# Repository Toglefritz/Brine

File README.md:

# Brine

# Hello :wave:

Do you ever forget to refill the salt in your water softener? Yes you do. It is probably a safe
bet to say that everybody who has a water softener in their home forgets to refill the salt from
time to time. That "time to time" might even be several months in row.

The Brine water softener monitor keeps track of the amount of salt remaining in your water softener
and delivers alerts when the level is low. With this tool, you can keep your water softener filled
with salt and working properly, which, in turn, will keep your appliances free of mineral deposits,
your hands and hair well-moisturized, your laundry machine effective, and spots off your dishes.

# Overview 

Brine is an IoT water softener monitor. It tracks the amount of salt remaining in a water softener
and delivers alerts when the level is low, keeping your appliances free of mineral deposits, your
hands and hair well-moisturized, your laundry machine effective, and spots off your dishes.

The project spans hardware, firmware, a mobile companion app, cloud backend services, and a
marketing website.

## Project Status

> **Hardware finalization and pre-manufacturing**
>
> The hardware design is being finalized ahead of final system integration.
> Preparation for first-run manufacturing is underway.

## How It Works

A Brine device mounts inside the lid of a water softener, facing down toward the salt. It uses a
VL53L1X distance sensor to measure the distance from the top of the softener to the salt surface,
then calculates an approximate percentage of salt remaining. The device wakes from deep sleep once
every 24 hours to take a measurement, report it to the cloud, and go back to sleep.

Users set up a Brine device through the companion mobile app using Bluetooth Low Energy. The app
walks through pairing, WiFi provisioning, and account association. Once provisioned, the app
displays a dashboard with salt level, battery level, and device information, and delivers push
notifications when levels are low.

## Repository Structure

| Directory | Description |
|---|---|
| [`brine_app`](brine_app/) | Flutter companion app for iOS, Android, and macOS. Handles device provisioning via BLE and displays device status on a dashboard. |
| [`brine_firmware`](brine_firmware/) | ESP32 firmware built with PlatformIO and the Arduino framework. Manages the distance sensor, battery monitoring, BLE communication, and deep sleep. |
| [`brine_cloud_functions`](brine_cloud_functions/) | Firebase Cloud Functions that form the backend infrastructure. Handles device registration, data ingestion, and push notifications. |
| [`brine_website`](brine_website/) | Flutter web marketing site for the Brine product. |
| [`brine_docs`](brine_docs/) | Project documentation covering OTA updates, power management, provisioning, and security. |
| [`brine_electronics`](brine_electronics/) | PCB designs, Gerber files, prototypes, and reference materials for the Brine hardware. |
| [`brine_cad`](brine_cad/) | 3D models and drawings for the device enclosure (Plasticity, STEP, and STL formats). |
| [`brine_logos`](brine_logos/) | Brand assets and logo files in various formats. |
| [`brine_store_listings`](brine_store_listings/) | App store listing assets including screenshots and feature graphics. |
| [`brine_dev_tui`](brine_dev_tui/) | Terminal UI launcher for starting development tools (firmware flashing, emulator, serial monitor, Flutter app, Firebase emulator). |

## Development Launcher

The project includes a terminal UI for launching the various tools needed during local development.
Instead of remembering individual commands across multiple directories, the launcher provides a
single interface to start everything from one place.

Double-click `brine_dev_tui/Brine Launcher.command` in Finder to build and run it, or from the
terminal:

```sh
cd brine_dev_tui
go build -o brine-launcher .
./brine-launcher
```

See [`brine_dev_tui/README.md`](brine_dev_tui/README.md) for controls and architecture details.

## Technology Overview

- **Firmware**: C++ on ESP32 via PlatformIO / Arduino framework
- **Mobile App**: Flutter (Dart), targeting iOS, Android, and macOS
- **Backend**: Firebase (Cloud Functions, Firestore, Authentication, Cloud Messaging)
- **Website**: Flutter Web, hosted on Firebase Hosting
- **Hardware**: Custom PCB with ESP32 and VL53L1X distance sensor, powered by rechargeable LiPo battery
- **CAD**: Plasticity for enclosure design

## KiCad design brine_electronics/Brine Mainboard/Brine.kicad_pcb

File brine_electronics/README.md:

# Brine

PCB design and hardware reference for the Brine Monitor, an IoT device that monitors the amount of
salt remaining in a water softener.

## Hello :wave:

Do you ever forget to refill the salt in your water softener? Yes you do. It is probably a safe
bet to say that everybody who has a water softener in their home forgets to refill the salt from
time to time. That "time to time" might even be several months in row.

The Brine water softener monitor keeps track of the amount of salt remaining in your water softener
and delivers alerts when the level is low. With this tool, you can keep your water softener filled
with salt and working properly, which, in turn, will keep your appliances free of mineral deposits,
your hands and hair well-moisturized, your laundry machine effective, and spots off your dishes.

## Hardware Overview

The Brine device is a battery-powered sensor board built around a Seeed Studio XIAO ESP32-S3
module. It measures the distance from the top of a water softener to the salt surface using a
VL53L1X time-of-flight distance sensor, then reports that measurement to the cloud over WiFi.

The board includes:

- XIAO ESP32-S3 microcontroller module (WiFi, BLE, and GPIO)
- VL53L1X time-of-flight distance sensor connected over I2C
- Battery power input with a voltage divider for battery level monitoring
- A physical button for entering setup mode and waking from deep sleep
- An RGB LED for status indication during provisioning and operation

The PCB is a two-layer board designed to fit inside a custom enclosure. Enclosure models are
maintained separately in the [`brine_cad`](../brine_cad/) directory.

## KiCAD Project

The active design lives in the `Brine Mainboard/` directory and is a KiCAD 9 project.

### Hierarchical Schematic Structure

The schematic is organized as a set of hierarchical sheets. The root sheet (`Brine.kicad_sch`)
acts as a block diagram of the hardware, showing each functional block and the signals that
connect them. Each block is defined in its own schematic sheet with the full circuit detail for
that subsystem.

| Sheet | File | Description |
|---|---|---|
| Root | `Brine.kicad_sch` | Top-level block diagram showing all subsystems and their interconnections. |
| XIAO ESP32-S3 | `xiao_esp32-s3.kicad_sch` | Microcontroller module pinout and connections to all peripheral blocks. |
| Battery | `brine_battery.kicad_sch` | Battery input and power delivery. |
| Button | `brine_button.kicad_sch` | Physical pushbutton circuit for user interaction and wake-from-sleep. |
| RGB LED | `brine_rgb_led.kicad_sch` | Status LED driven by the microcontroller. |
| Battery Monitor | `brine_battery_monitor.kicad_sch` | Voltage divider circuit for reading battery level on an analog input. |
| Distance Sensor | `brine_distance_sensor.kicad_sch` | VL53L1X time-of-flight sensor with I2C and shutdown control lines. |

The root sheet is the best starting point for understanding how the subsystems relate to each
other. Open it in KiCAD's schematic editor to see the block-level signal flow, then navigate into
individual sheets for component-level detail.

### PCB Layout

The PCB (`Brine.kicad_pcb`) is a two-layer board. A 3D STEP model of the board (`Brine.step`) is
included for use in enclosure design and fit verification.

Production outputs, including Gerbers, BOM, and pick-and-place position files, are generated into
the `production/` subdirectory.

## Directory Structure

| Directory | Description |
|---|---|
| `Brine Mainboard/` | Active KiCAD project containing schematics, PCB layout, production outputs, and the board STEP model. |
| `Libraries/` | Custom KiCAD symbol and footprint libraries for components not available in the default KiCAD libraries (e.g., VL53L1X). |
| `Gerbers/` | Legacy Gerber output directory. Current production files are generated into `Brine Mainboard/production/`. |
| `Archive/` | Previous board revisions and design iterations, including earlier EAGLE-based designs. Kept for reference. |

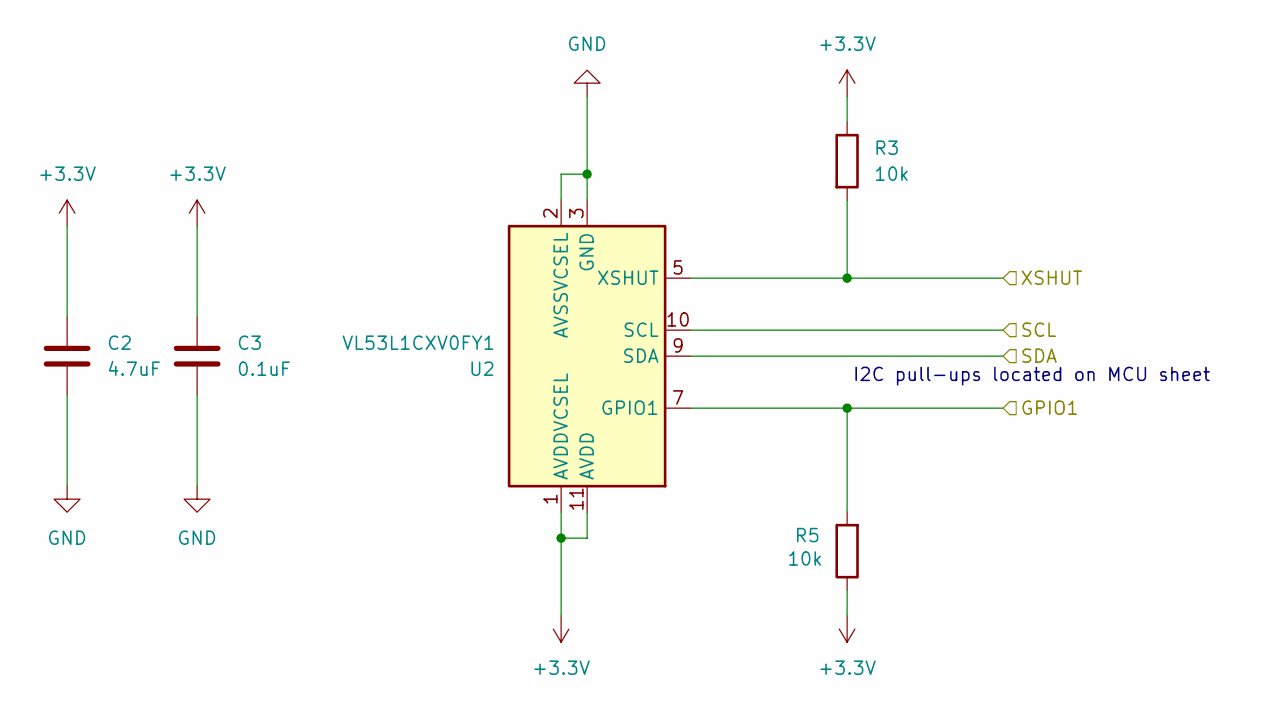
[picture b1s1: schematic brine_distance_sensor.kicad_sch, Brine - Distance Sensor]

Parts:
C2: 4.7uF; C_0805_2012Metric; LCSC Part # C1746
C3: 0.1uF; C_0805_2012Metric; LCSC Part # C1711
R3, R5: 10k; R_0805_2012Metric; LCSC Part # C17414
U2: VL53L1CXV0FY1; LCSC Part # C190004

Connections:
+3.3V: C2.1, C3.1, R3.1, R5.1, U2.1 (AVDDVCSEL), U2.11 (AVDD); also elsewhere on the board
/Distance Sensor/GPIO1: R5.2, U2.7 (GPIO1); also elsewhere on the board
/Distance Sensor/SCL: U2.10 (SCL); also elsewhere on the board
/Distance Sensor/SDA: U2.9 (SDA); also elsewhere on the board
/Distance Sensor/XSHUT: R3.2, U2.5 (XSHUT); also elsewhere on the board
GND: C2.2, C3.2, U2.2 (AVSSVCSEL), U2.3 (GND), U2.4 (GND), U2.6 (GND), U2.12 (GND); also elsewhere on the board

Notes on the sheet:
I2C pull-ups located on MCU sheet

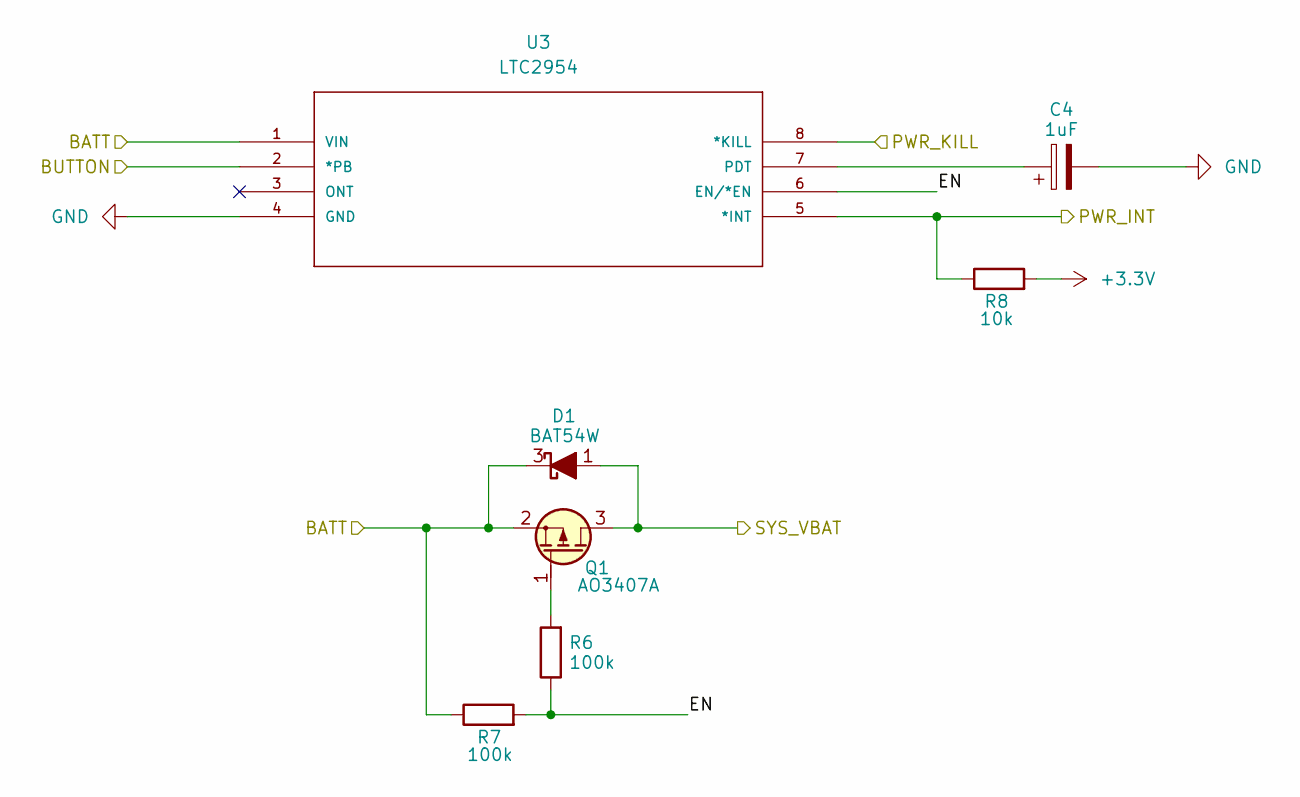
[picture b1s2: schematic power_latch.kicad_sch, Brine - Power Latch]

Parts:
C4: 1uF; CP_EIA-2012-12_Kemet-R; LCSC Part # C1952822
D1: BAT54W; SOT-323_SC-70; LCSC Part # C8657
Q1: AO3407A; SOT-23; LCSC Part # C347478
R6, R7: 100k; R_0805_2012Metric; LCSC Part # C25611
R8: 10k; R_0805_2012Metric; LCSC Part # C17414
U3: LTC2954; TSOT-23_TS8; MANUFACTURER_PART_NUMBER ltc2954cts81; LCSC Part # C580656

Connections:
+3.3V: R8.2; also elsewhere on the board
/Battery Monitor/SYS_VBAT: D1.1 (A), Q1.3 (D); also elsewhere on the board
/Battery/BATT: D1.3 (K), Q1.2 (S), R7.1, U3.1 (VIN); also elsewhere on the board
/Button/BUTTON: U3.2 (*PB); also elsewhere on the board
/Power Latch/EN: R6.1, R7.2, U3.6 (EN/*EN)
/Power Latch/PWR_INT: R8.1, U3.5 (*INT); also elsewhere on the board
/Power Latch/PWR_KILL: U3.8 (*KILL); also elsewhere on the board
GND: C4.2, U3.4 (GND); also elsewhere on the board
unnamed: Q1.1 (G), R6.2
unnamed: C4.1, U3.7 (PDT)

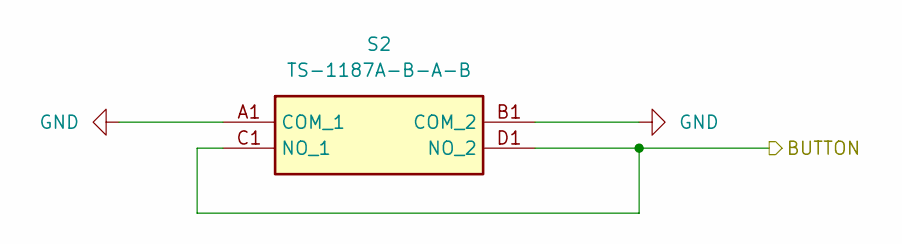
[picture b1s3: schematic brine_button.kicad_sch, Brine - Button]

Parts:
S2: TS-1187A-B-A-B; TS1187ABAB; LCSC Part # C318884

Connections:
/Button/BUTTON: S2.C1 (NO_1), S2.D1 (NO_2); also elsewhere on the board
GND: S2.A1 (COM_1), S2.B1 (COM_2); also elsewhere on the board

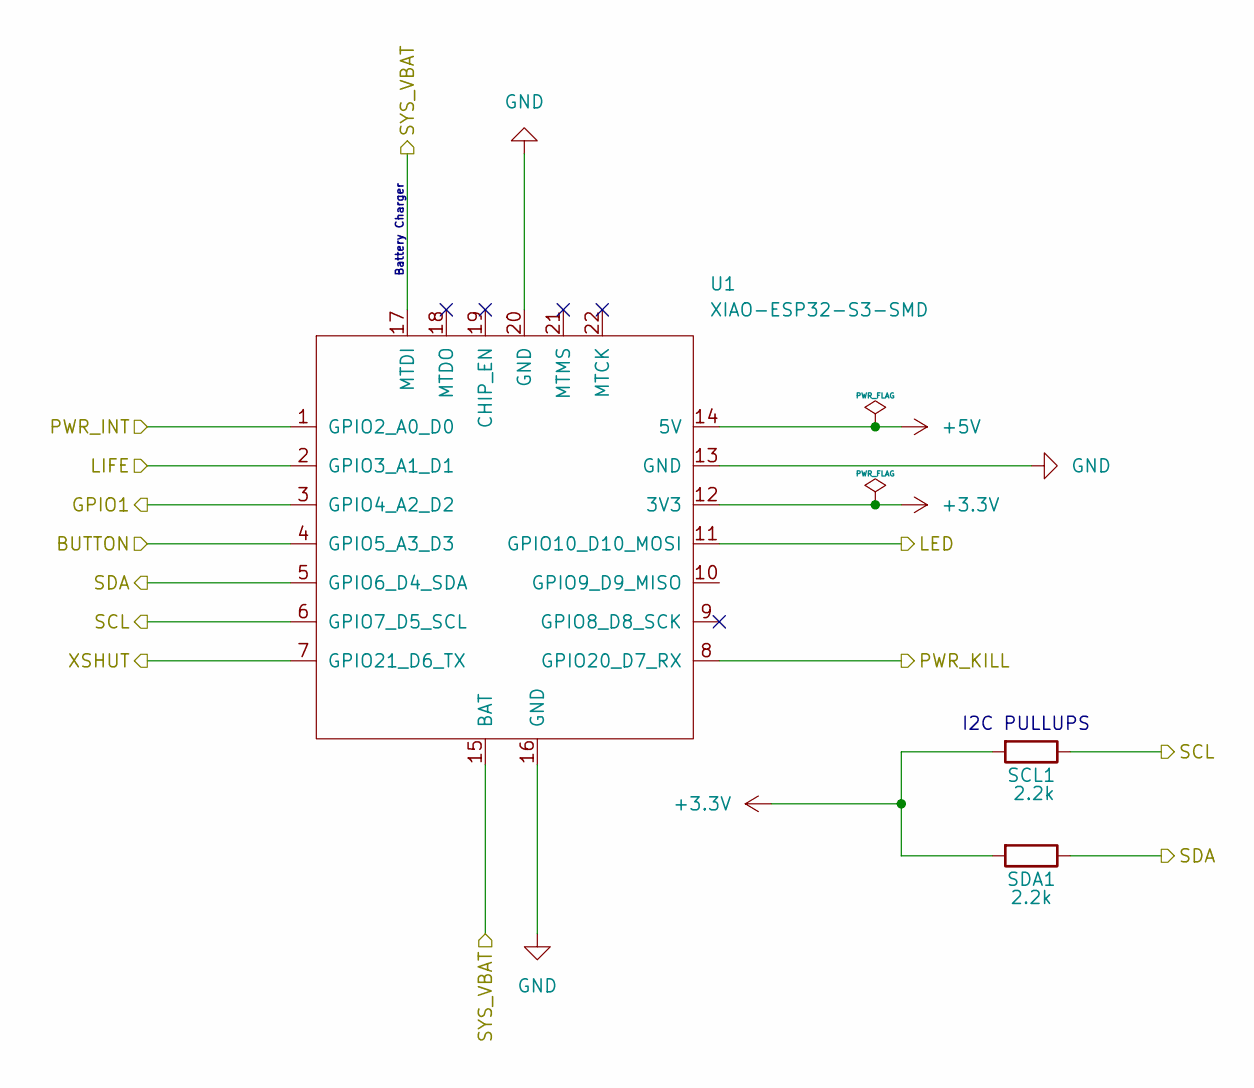
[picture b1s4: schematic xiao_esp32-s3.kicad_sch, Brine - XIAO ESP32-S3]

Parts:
SCL1: 2.2k; R_0805_2012Metric; LCSC Part # C17520
SDA1: 2.2k; R_0805_2012Metric; LCSC Part # C17520
U1: XIAO-ESP32-S3-SMD; XIAO-ESP32S3-DIP

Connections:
+3.3V: SCL1.2, SDA1.2, U1.12 (3V3); also elsewhere on the board
+5V: U1.14 (5V); also elsewhere on the board
/Battery Monitor/LIFE: U1.2 (GPIO3_A1_D1); also elsewhere on the board
/Button/BUTTON: U1.4 (GPIO5_A3_D3); also elsewhere on the board
/Distance Sensor/GPIO1: U1.3 (GPIO4_A2_D2); also elsewhere on the board
/Distance Sensor/SCL: SCL1.1, U1.6 (GPIO7_D5_SCL); also elsewhere on the board
/Distance Sensor/SDA: SDA1.1, U1.5 (GPIO6_D4_SDA); also elsewhere on the board
/Distance Sensor/XSHUT: U1.7 (GPIO21_D6_TX); also elsewhere on the board
/Power Latch/PWR_INT: U1.1 (GPIO2_A0_D0); also elsewhere on the board
/Power Latch/PWR_KILL: U1.8 (GPIO20_D7_RX); also elsewhere on the board
/RGB LED/LED: U1.11 (GPIO10_D10_MOSI); also elsewhere on the board
GND: U1.13 (GND), U1.16 (GND), U1.20 (GND); also elsewhere on the board

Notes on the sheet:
I2C PULLUPS
Battery Charger

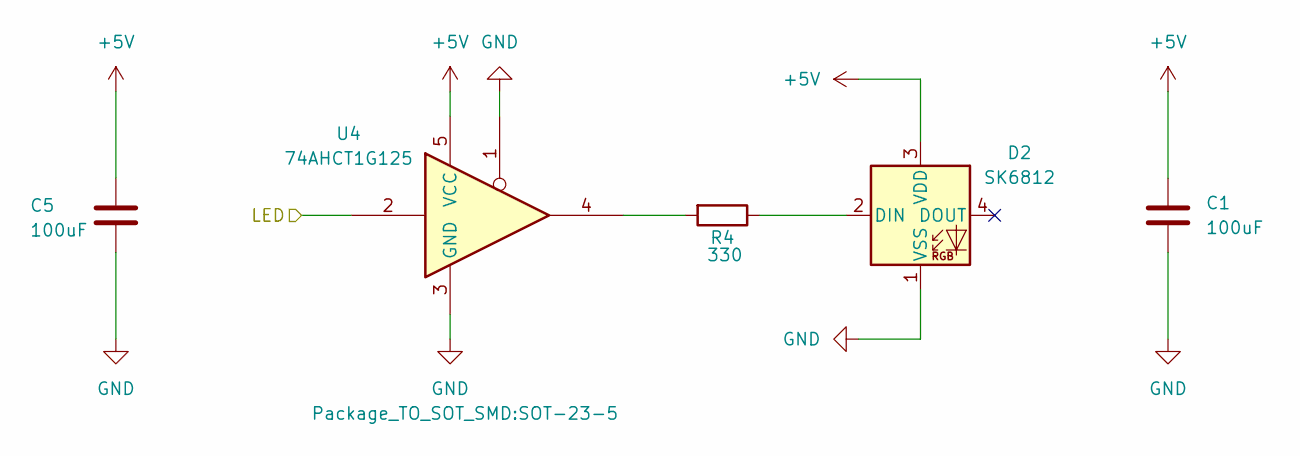
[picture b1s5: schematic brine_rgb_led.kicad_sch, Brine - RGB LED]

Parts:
C1, C5: 100uF; C_0805_2012Metric; LCSC Part # C141660
D2: SK6812; LED_SK6812_PLCC4_5.0x5.0mm_P3.2mm; LCSC Part # C5378720
R4: 330; R_0805_2012Metric; LCSC Part # C212379
U4: 74AHCT1G125; SOT-23-5; LCSC Part # C52140417

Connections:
+5V: C1.1, C5.1, D2.3 (VDD), U4.5 (VCC); also elsewhere on the board
/RGB LED/LED: U4.2; also elsewhere on the board
GND: C1.2, C5.2, D2.1 (VSS), U4.1, U4.3 (GND); also elsewhere on the board
unnamed: D2.2 (DIN), R4.1
unnamed: R4.2, U4.4

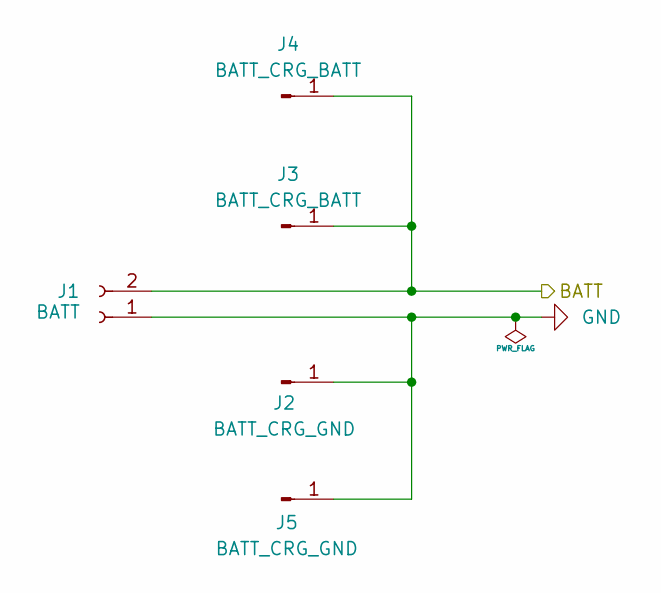
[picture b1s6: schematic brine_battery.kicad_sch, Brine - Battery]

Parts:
J1: BATT; JST_PH_S2B-PH-K_1x02_P2.00mm_Horizontal
J2: BATT_CRG_GND; SolderWirePad_1x01_SMD_1.5x3mm
J3: BATT_CRG_BATT; SolderWirePad_1x01_SMD_1.5x3mm
J4: BATT_CRG_BATT; PinHeader_1x01_P1.00mm_Vertical
J5: BATT_CRG_GND; PinHeader_1x01_P1.00mm_Vertical

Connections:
/Battery/BATT: J1.2, J3.1 (Pin_1_1), J4.1 (Pin_1_1); also elsewhere on the board
GND: J1.1, J2.1 (Pin_1_1), J5.1 (Pin_1_1); also elsewhere on the board

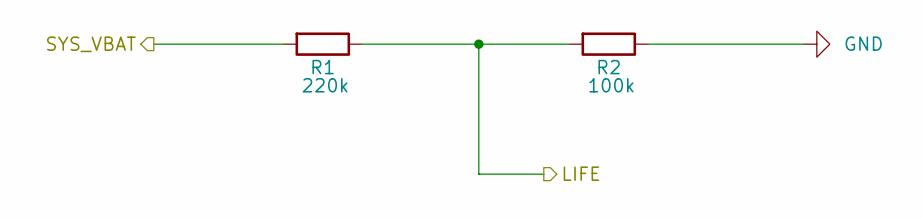
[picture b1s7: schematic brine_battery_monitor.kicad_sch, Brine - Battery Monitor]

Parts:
R1: 220k; R_0805_2012Metric; LCSC Part # C17556
R2: 100k; R_0805_2012Metric; LCSC Part # C25611

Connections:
/Battery Monitor/LIFE: R1.1, R2.2; also elsewhere on the board
/Battery Monitor/SYS_VBAT: R1.2; also elsewhere on the board
GND: R2.1; also elsewhere on the board

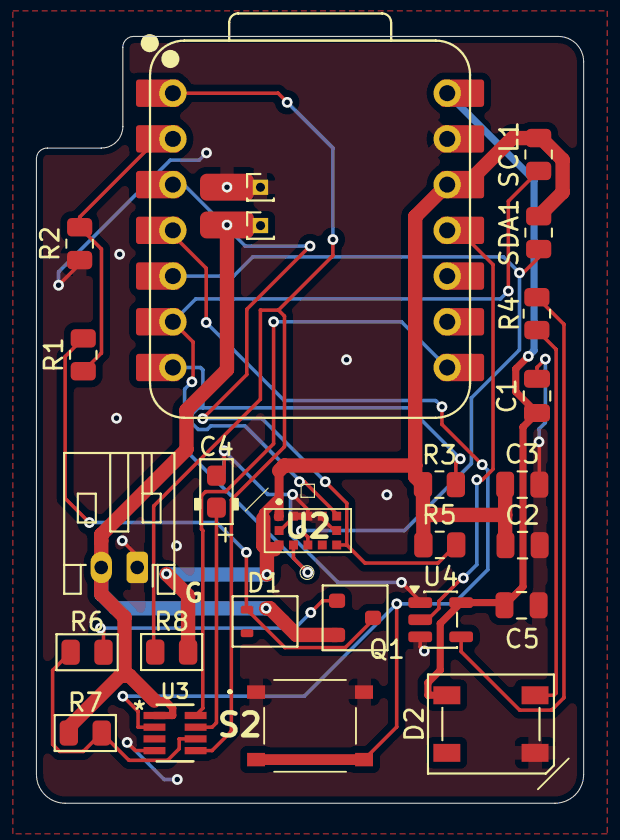
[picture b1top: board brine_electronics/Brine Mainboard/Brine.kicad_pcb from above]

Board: 2 copper layers, 30.4 x 42.6 mm, 28 parts (0 on the bottom side), 19 nets.

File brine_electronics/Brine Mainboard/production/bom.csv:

Designator,Footprint,Quantity,Value,LCSC Part #
"C1, C5",0805,2,100uF,
C2,0805,1,4.7uF,
C3,0805,1,0.1uF,
C4,CP_EIA-2012-12_Kemet-R,1,1uF,
D1,SOT-323_SC-70,1,BAT54W,
D2,LED_SK6812_PLCC4_5.0x5.0mm_P3.2mm,1,SK6812,
J1,JST_PH_S2B-PH-K_1x02_P2.00mm_Horizontal,1,BATT,
J2,SolderWirePad_1x01_SMD_1.5x3mm,1,BATT_CRG_GND,
J3,SolderWirePad_1x01_SMD_1.5x3mm,1,BATT_CRG_BATT,
J4,PinHeader_1x01_P1.00mm_Vertical,1,BATT_CRG_BATT,
J5,PinHeader_1x01_P1.00mm_Vertical,1,BATT_CRG_GND,
Q1,SOT-23,1,AO3407A,
R1,0805,1,220k,
"R2, R6, R7",0805,3,100k,
"R3, R5, R8",0805,3,10k,
R4,0805,1,330,
S2,TS1187ABAB,1,TS-1187A-B-A-B,
"SCL1, SDA1",0805,2,2.2k,
U1,XIAO-ESP32S3-DIP,1,XIAO-ESP32-S3-SMD,
U2,VL53L1CXV0FY1,1,VL53L1CXV0FY1,
U3,TSOT-23_TS8,1,LTC2954,
U4,SOT-23-5,1,74AHCT1G125,

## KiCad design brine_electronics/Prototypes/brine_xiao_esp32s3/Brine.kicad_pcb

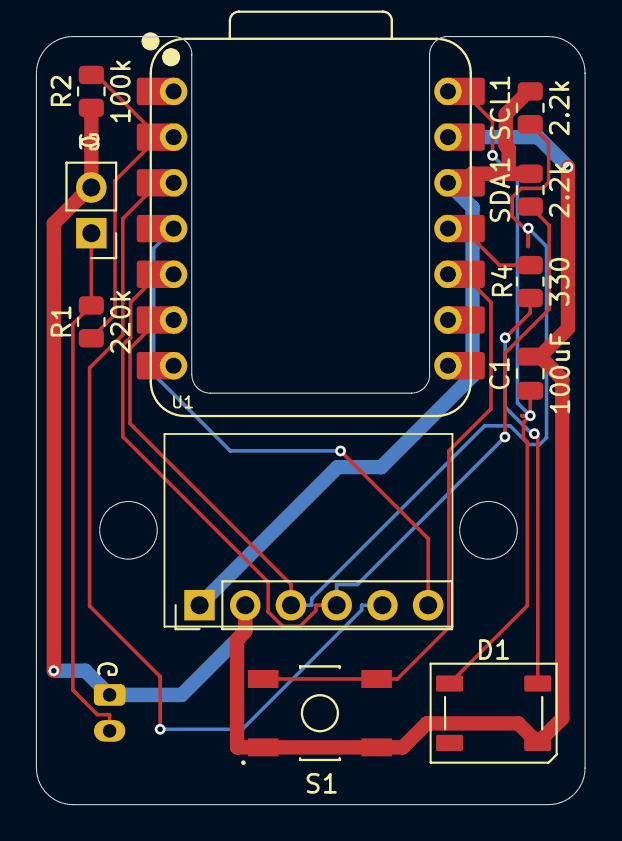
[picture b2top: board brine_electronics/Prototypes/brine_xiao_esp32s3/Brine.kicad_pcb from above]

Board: 2 copper layers, 30.5 x 42.7 mm, 14 parts (1 on the bottom side), 12 nets.

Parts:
BATT1: Conn_01x02_Pin; PinHeader_1x02_P2.54mm_Vertical
C1: 100uF; C_0805_2012Metric
D1: WS2812B; LED_WS2812B_PLCC4_5.0x5.0mm_P3.2mm
H1, H2: MountingHole; MountingHole_3.2mm_M3
J1: Conn_01x02_Socket; JST_PH_B2B-PH-K_1x02_P2.00mm_Vertical
J2: VL53L1X; PinHeader_1x06_P2.54mm_Vertical
R1: 220k; R_0805_2012Metric
R2: 100k; R_0805_2012Metric
R4: 330; R_0805_2012Metric
S1: TL3342F260QG; SW_TL3342F160QG
SCL1: 2.2k; R_0805_2012Metric
SDA1: 2.2k; R_0805_2012Metric
U1: XIAO-ESP32-S3-SMD; XIAO-ESP32S3-DIP

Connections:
+3.3V: J2.1, SCL1.2, SDA1.2, U1.12 (3V3)
+5V: C1.1, D1.1 (VDD), U1.14 (5V)
BATT: BATT1.1, J1.2, R1.2
BUTTON: S1.3, S1.4, U1.10 (GPIO8_A9_D9_MISO)
GND: BATT1.2, C1.2, D1.3 (VSS), J1.1, J2.2, R2.1, S1.1, S1.2, U1.13 (GND)
GPIO1: J2.5, U1.3 (GPIO3_A2_D2)
LED: R4.2, U1.11 (GPIO9_A10_D10_MOSI)
LIFE: R1.1, R2.2, U1.2 (GPIO2_A1_D1)
unnamed: D1.4 (DIN), R4.1
SCL: J2.3, SCL1.1, U1.6 (GPIO6_A5_D5_SCL)
SDA: J2.4, SDA1.1, U1.5 (GPIO5_A4_D4_SDA)
XSHUT: J2.6, U1.4 (GPIO4_A3_D3)

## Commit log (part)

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2023-06-07 :lock: Added authentication to addLead function
2023-06-15 :sparkles: Added thanks screen :sparkles:
2023-06-17 :mechanical_arm: Added setup screen and device(s) retrieval methods
2023-06-18 Code cleanup and commenting :broom:
2023-06-18 :wave: Created welcome screen :wave:
2023-06-20 :tophat: Created insider page
2023-06-20 :snail: Check for duplicated leads :snail:
2023-06-21 Added rounded corners to GIFs :white_circle:
2023-06-22 :milky_way: Created class to wrap inset values
2023-06-26 Overhauled landing page design :art:
2023-06-28 Created landing view for small screen sizes :iphone:
2023-06-28 :email: Updated email opt-in form
2023-06-29 Removed unused GIF :test_tube:
2023-07-02 Removed unused print statement :paw_prints:
2023-07-03 Updated dependencies :tropical_fish:
2023-07-03 Temporarily disabled AppCheck :white_check_mark:
2023-07-03 Updated dependencies :octopus:
2023-07-03 :ocean: Added wave progress indicator
2023-07-04 Added mobile app submodule for demo :iphone:
2023-07-04 Inverted progress indicator :repeat:
2023-07-04 Applied theme to app demo :art:
2023-07-04 Periodically update demo values :salt:
2023-07-04 Animate changes in salt level :flamingo:
2023-07-04 :point_right: Animate landing CTA button by default :point_left:
2023-07-04 Added additional form validation logic :clipboard:
2023-07-07 Added social sharing buttons :wave:
2023-07-08 Updated submodule reference :blowfish:
2023-07-08 Added Brine device info :brain:
2023-07-10 :pencil2: Updated device info table border
2023-07-10 Set display name for authenticated visitor :wave:
2023-07-12 :heavy_check_mark: Updated opt-in form validation
2023-07-15 Added product info :information_source:
2023-07-15 Added additional tagging :clipboard:
2023-07-16 :email: Added email share functionality
2023-07-16 :package: Submit opt-in form with enter button
2023-07-18 Added wrapper for analytics calls :candy:
2023-07-25 Added favicon :tropical_drink:
2023-07-25 Updated for Firebase deployment :fire:
2023-07-26 :scroll: Updated README
2023-07-30 Removed unused dependency :seal:
2023-07-30 Updated the icon for not-Twitter :bird:
2023-07-31 Updated sharing icon color :art:
2023-07-31 Removed eslint :wave:
2023-07-31 Updated confetti button text :confetti_ball:
2024-02-11 Added documentation about deep sleep mode
2024-02-22 Removed timeline :hourglass_flowing_sand:
2024-02-24 Created Dart Frog project :frog:
2024-02-28 Updated README :page_facing_up:
2024-02-28 Fixed a little overflow thing :octopus:
2024-03-05 Enabled AppCheck for iOS :white_check_mark:
2024-03-05 Updated createUser function to trigger off account creation
2024-03-06 Refactored Firebase resources into services :fire:
2024-03-09 Updated linter rules :soap:
2024-03-09 Updated README :newspaper:
2024-03-09 Converted device endpoints from callable functions to REST APIs :sleeping_bed:
2024-03-11 Updated salt level display :salt:
2024-03-11 Updated iOS app icon :art:
2024-03-12 Updated to CommonJS modules :sauropod:
2024-03-13 Updated dark theme :art:
2024-03-16 Removed unused dependency :axe:
2024-03-24 Added documentation about the provisioning flow :ocean:
2024-03-26 Initial commit. Created project organization and architectural documentation :rocket:
2024-03-29 Created debug service :abacus:
2024-03-29 Updated debug service to use build system flags :triangular_flag_on_post:
2024-03-29 Created button library :zap:
2024-04-02 Created LED service :bulb:
2024-04-02 Created test for LED service :test_tube:
2024-04-03 Updated LED module test :candle:
2024-04-06 Split button and LED tests into different suites :card_index_dividers:
2024-04-06 Added distance sensor library :straight_ruler:
2024-04-07 Automated LED test :mechanical_arm:
2024-04-07 Updated DeviceManager with DistanceSensor interface :straight_ruler:
2024-04-10 Created BLE library and test :large_blue_circle:
2024-04-15 Updated provisioning process timeout :hourglass_flowing_sand:
2024-04-19 Created provisioning manager :clapper:
2024-04-21 Added MacOS support :apple:
2024-04-21 Updated onboarding page layout :triangular_ruler:
2024-04-24 Added BLE scan route :satellite:
2024-05-11 Added launch image :art:
2024-05-14 Updated provider account creation process :link:
2024-05-17 Added analytics and Crashlytics :mag:
2024-05-28 Updated dependencies :whale2:
2024-05-28 Updated image assets reference :camera:
2024-05-29 Check for Bluetooth permissions and status :smile_cat:
2024-05-29 Updated dark theme :new_moon:
2024-06-01 Fixed issue preventing second provisioning attempt :two:
2024-06-01 Updated Bluetooth discovery process :mag:
2024-06-01 Added device confirmation route :+1:
2024-06-03 Added BLE connection process :robot:
2024-06-05 Updated Bluetooth system :large_blue_circle:
2024-06-08 Updated Bluetooth system :large_blue_diamond:
2024-06-11 Include primary UUID in advertisement data :package:
2024-06-15 Replaced deprecated API calls :wrench:
2024-06-15 Get Brine device ID :salt:
2024-06-15 Added account association request :elephant:
2024-06-15 Create device record during association :elephant:
2024-06-15 Updated BLE module test :large_blue_circle:
2024-06-18 Added WiFi scan command :satellite:
2024-06-18 Added WiFi scan BLE API :satellite:
2024-06-19 Added WiFi password fields :lock:
2024-06-22 Send WiFi connect command :globe_with_meridians:
2024-06-22 Set WiFi hostname :goat:
2024-06-22 Created WiFi service :globe_with_meridians:
2024-06-23 Updated handling of Firebase Emulator Suite IPs :fire:
2024-06-24 Refactored device configuration screens :game_die:
2024-08-13 Created appliance measurement route :triangular_ruler:
2024-08-13 Updated dependencies :fish:
2024-08-13 Added script for managing emulator suite :abacus:
2024-08-13 Removed addLead function :no_entry:
2024-08-13 Updated level management endpoints :salt:
2024-08-20 Updated function definitions, authentication :t-rex:
2024-08-20 Updated lint rules :soap:
2024-08-21 Added device management test :dna:
2024-08-23 Refactored device communication service class name :rose:
2024-08-23 Created BrineDevice class test :test_tube:
2024-08-25 Updated macOS build configuration :apple:
2024-08-25 Updated auth middleware :lock:
2024-08-26 Updated BT search timeout :satellite:
2024-08-27 Added command to get public key :large_blue_circle:
2024-08-27 Include Brine public key in account association :key:
2024-08-28 Updated provisioning flow parameters :sauropod:
2024-08-29 Updated provisioning documentation :coffee:
2024-09-17 Updated CryptoService test :petri_dish:
2024-09-25 Updated provisioning documentation :scroll:
2024-10-06 Added command to end provisioning :checkered_flag:
2024-10-06 Updated getDevice endpoint :zap:
2024-10-06 Updated salt level display :triangular_ruler:
2024-10-06 Updated key for salt distance update :key:
2024-10-12 Added NVS service :brain:
2024-10-12 Get WiFi creds from NVS :brain:
2024-10-12 Added system reset button long press :recycle:
2024-12-21 Updated FES IP address 🔥
2024-12-22 Added deep sleep management service :bed:
2024-12-26 Updated battery level monitor service 🔋
2025-01-01 Added flag for Firebase flavor :bacon:
2025-01-01 Updated battery monitor test 🔋
2025-01-02 Stop distance sensor after getting reading 📏
2025-01-08 Added I2C scanner test :test_tube:
2025-01-11 Added full system test :test_tube:
2025-01-14 Updated system reset process 🐡
2025-01-14 Removed public key usage 🔑
2025-01-14 Get PSK and transfer to Brine :old_key:
2025-01-15 Updated documentation for HMAC usage :closed_lock_with_key:
2025-01-15 Added HMAC based authentication :closed_lock_with_key:
2025-01-15 Added PSK management to provisioning flow :closed_lock_with_key:
2025-01-23 Added screen for overdue updates :question:
2025-01-29 Updated function to get Brine devices :salt:
2025-02-05 Created account settings page 👤
2025-02-05 Updated documentation 📜
2025-02-07 Added ability to switch selected device :pretzel:
2025-02-08 Added ability to remove devices from account 🚫
2025-02-09 Added PNS capabilities :speech_balloon:
2025-02-09 Added ability to modify profile information 📝
2025-02-11 Added ability to delete account ⛔
2025-02-17 Added function for deleing user data 🚯
2025-04-09 Updated the codebase :soap:
2025-04-09 Removed submodule 🚫
2025-04-11 Updated add lead function ➕
2025-04-11 Created function for adding leads ➕
2025-04-17 Updated create account field :bust_in_silhouette:
2025-04-19 Updated Android app upload signing :black_nib:
2025-04-19 Updated salt level calculation :level_slider:
2025-04-22 Revert "Updated Android build :robot:"
    This reverts commit e6b66a63bb90128bd0cf2a86f18fe1160e2bd232.
2025-05-05 Updated salt level bounds :salt:
2025-05-05 Updated device update timestamp format 🕑
2025-06-24 Updated user documentation creation to HTTP endpoint :bust_in_silhouette:
2025-06-24 Created endpoint for user creation :bust_in_silhouette:
2025-06-30 Added authentication errors :rotating_light:
2025-10-07 Added function tests :petri_dish:
2025-10-07 Created VS Code launch configuration
2025-10-09 Updated SDK version ☝️
2025-10-30 Added service for WS2812B LED 💡
2025-11-01 Renamed distance sensor services 📏
2025-11-01 Implemented voltage divider battery monitor 🔋
2025-11-01 Updated distance sensor test 📐
2025-11-15 Commented unused environment 💬
2025-11-27 Updated GPIO button test 👇
2025-11-27 Replaced deprecated API calls ✨
2025-11-27 Updated LED color for provisioning 🔵
2025-11-27 Added OTA documentation 🆙
2025-11-28 Updated device management service for production endpoints 🌐
2025-11-29 Initial OTA implementation 🆙
2025-11-29 Updated deep sleep management :sleeping_bed:
2025-11-29 Transfer PSK in chunks 🔒
2025-11-29 Defer BLE responses to the main stack 🔵
2025-11-30 Refactor BLE command handling to use deferred execution pattern :large_blue_circle:
2025-11-30 Revert "Transfer PSK to Brine device in chunks 🔒"
    This reverts commit e0f4909b53c8fe45753a6efee2a0f0754c76cb96.
2025-11-30 Updated Firebase REST requests 🔥
2026-03-18 Created firmware emulator :cat2:
2026-03-20 Add brine_cad to unified repo
2026-03-20 Add brine_electronics to unified repo
2026-03-20 Add brine_logos to unified repo
2026-03-20 Updated localization dependencies 🌐
2026-03-20 Created top-level README 📖
2026-03-21 Wired firmware development commands ⚡
2026-03-21 Wired app and cloud launch commands 📱
2026-03-21 Created TUI launch command 🚀
2026-04-03 Created integrated distance sensor
2026-04-03 Created Gerbers ⚡
2026-04-05 Updated cloud documentation ☁️
2026-04-05 Created website maintenance mage 🚧
2026-04-05 Reorganized components 📁
2026-04-05 Fixed linter issues ✅
2026-04-05 Check HMAC signature during OTA process 🔒
2026-04-05 Removed unused backups :wastebasket:
2026-04-06 Updated PCB retention bosses 📐
2026-04-08 Implemented power latch circuit ⚡
2026-04-12 Added project status statement 🚦
2026-04-18 Updated PCB manufacturing files :mechanical_arm:
2026-05-04 Updated lower latch circuit ⚡
2026-05-05 Implemented power latch service ⚡
2026-05-05 Updated documentation 📄
2026-05-06 Added support for SK6812 💡
2026-05-07 Updated GPIO button wiring ⚡
2026-05-12 Updated button connection 👇
2026-05-13 Updated welcome screen layout 👋
2026-05-13 Updated tests :test_tube:
2026-05-13 Updated code formatting 📐
2026-05-13 Moved Actions pipeline :package:
2026-05-13 Updated test runner platform 🍎
2026-05-14 Updated node version :octopus:
2026-05-14 Added account screen tests :microscope:
2026-05-16 Created tests for error route :warning:
2026-05-16 Updated DI for account route 💉
2026-05-16 Created battery indicator test 🔋
2026-05-17 Implemented additional component and model tests :test_tube:
2026-05-17 Created association and PSK setup tests :alembic:
2026-05-17 Created device installation step tests :wrench:
2026-05-17 Created tests for provisioning complete step ✅
2026-05-17 Created initial BLE connection test 🔗
2026-05-17 Created WiFi setup tests :test_tube:
2026-05-17 Created regex tests :dna:
2026-05-18 Created service tests :test_tube:
2026-05-20 Updated distance sensor routing 📏
2026-05-26 Updated electronics production files 🏭
2026-06-14 Updated distance sensor test 📏
